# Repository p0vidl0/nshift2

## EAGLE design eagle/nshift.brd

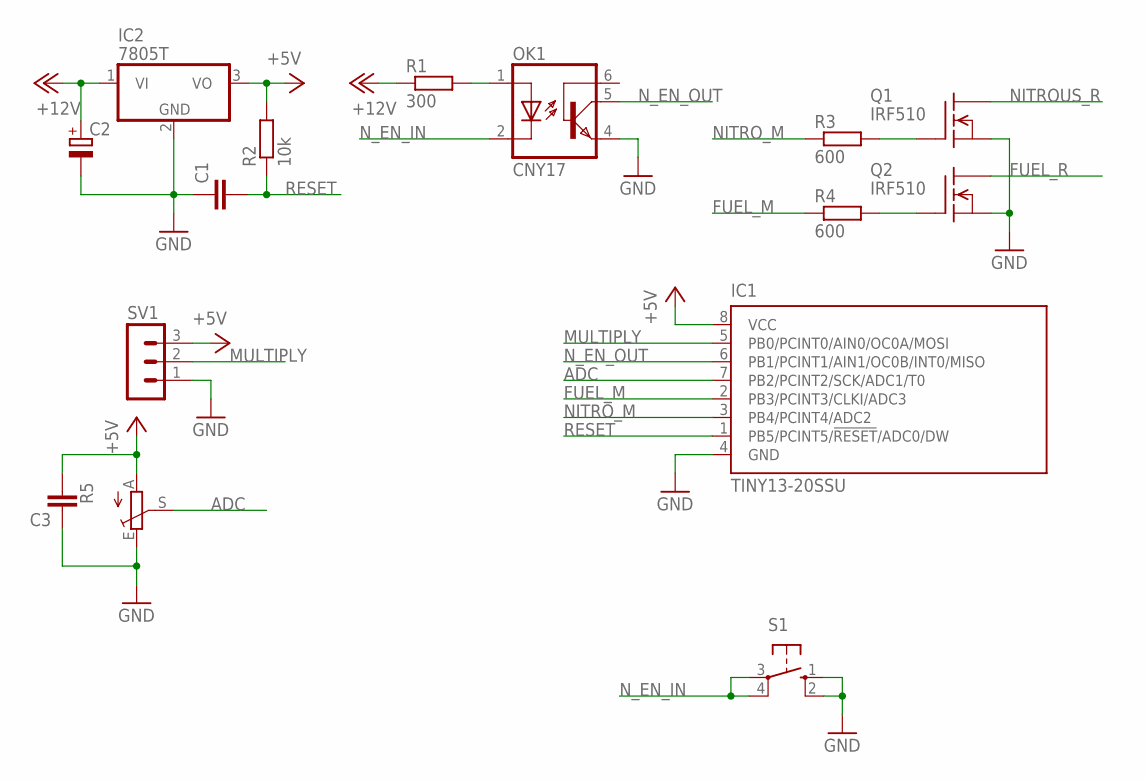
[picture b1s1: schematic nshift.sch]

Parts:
C1, C3: C-EUC1206; C1206
C2: CPOL-EUE2.5-7; E2,5-7
IC1: TINY13-20SSU; 8S1
IC2: 7805T; TO220H
OK1: CNY17; DIL06
Q1, Q2: IRF510; TO220
R1: 300; R1206
R2: 10k; R1206
R3, R4: 600; R1206
R5: TRIM_EU-CA9V; CA9V
S1: 10-XX; B3F-10XX
SV1: MA03-1

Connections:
+5V: C3.2, IC1.8 (VCC), IC2.3 (VO), R2.2, R5.A, SV1.3
+12V: C2.+, IC2.1 (VI), R1.1
ADC: IC1.7 (PB2/PCINT2/SCK/ADC1/T0), R5.S
FUEL_M: IC1.2 (PB3/PCINT3/CLKI/ADC3), R4.1
FUEL_R: Q2.2 (D)
GND: C1.1, C2.-, C3.1, IC1.4 (GND), IC2.2 (GND), OK1.4 (EMI), Q1.3 (S), Q2.3 (S), R5.E, S1.1 (S), S1.2 (S1), SV1.1
MULTIPLY: IC1.5 (PB0/PCINT0/AIN0/OC0A/MOSI), SV1.2
unnamed: OK1.1 (A), R1.2
unnamed: Q2.1 (G), R4.2
unnamed: Q1.1 (G), R3.2
NITROUS_R: Q1.2 (D)
NITRO_M: IC1.3 (PB4/PCINT4/ADC2), R3.1
N_EN_IN: OK1.2 (C), S1.3, S1.4 (P1)
N_EN_OUT: IC1.6 (PB1/PCINT1/AIN1/OC0B/INT0/MISO), OK1.5 (COL)
RESET: C1.2, IC1.1 (PB5/PCINT5/!RESET!/ADC0/DW), R2.1

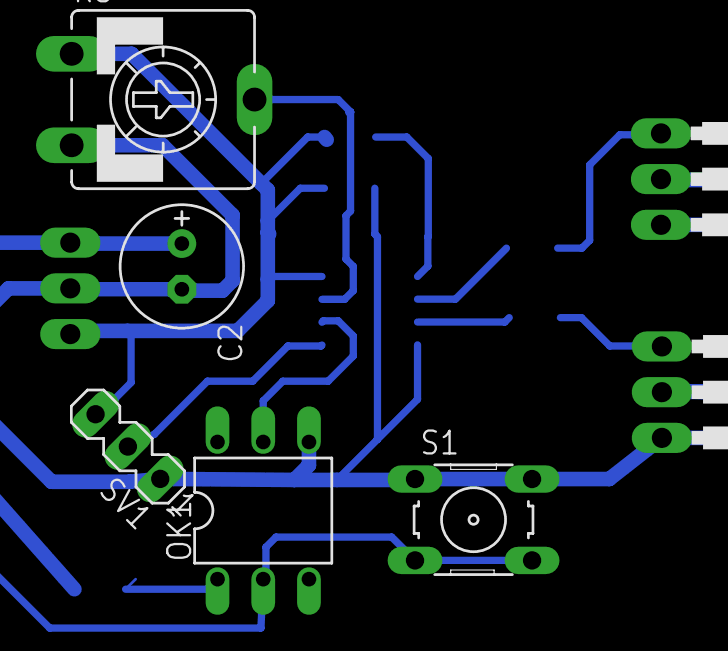
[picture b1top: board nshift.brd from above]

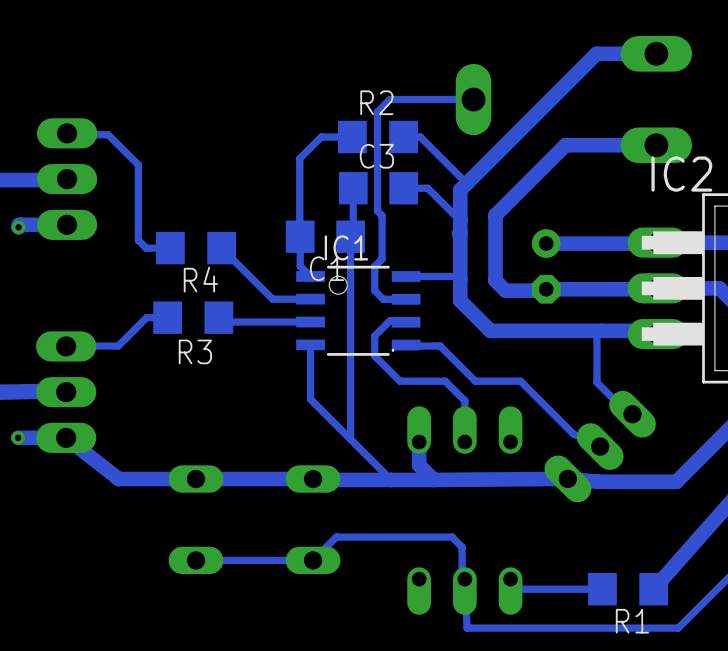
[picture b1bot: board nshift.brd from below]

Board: 2 copper layers, 15 parts (8 on the bottom side), 13 nets.

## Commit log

2017-06-30 init code
2017-06-30 update docs
2017-06-30 add eagle scheme
2017-06-30 fix gitignore
2017-06-30 refactor for new soic components
2017-06-30 Готовая плата soic
